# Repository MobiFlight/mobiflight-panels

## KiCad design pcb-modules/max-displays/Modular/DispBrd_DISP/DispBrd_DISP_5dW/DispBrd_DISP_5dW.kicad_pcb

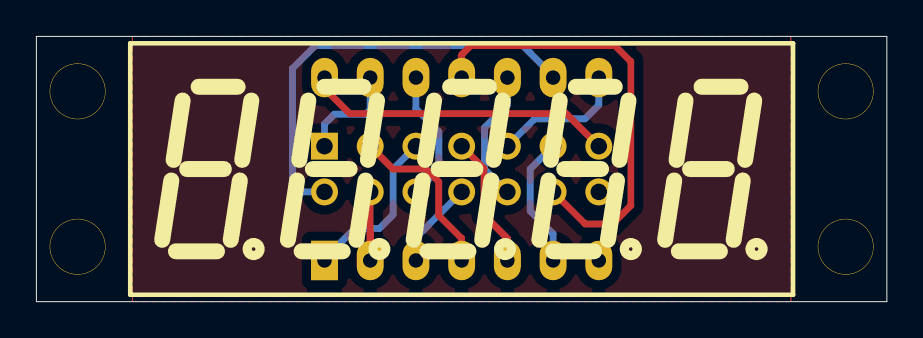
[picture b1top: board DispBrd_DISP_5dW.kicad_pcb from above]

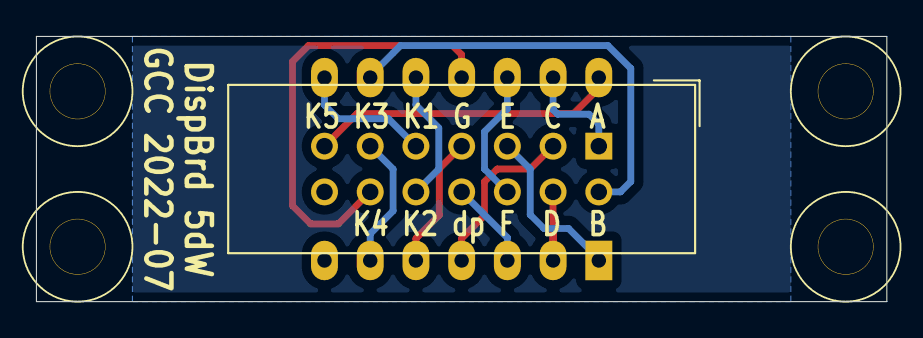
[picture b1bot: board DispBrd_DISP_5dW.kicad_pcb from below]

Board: 2 copper layers, 47.2 x 14.7 mm, 6 parts (5 on the bottom side), 13 nets.

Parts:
H5, H6, H7, H8: MountingHole; Hole3mm
P6: Disp5; IDC-Header_2x07_P2.54mm_Vertical
S4: LEDDSP5_CA; Disp7s5x_036

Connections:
/A0: P6.9, S4.8
/A1: P6.10, S4.10
/A2: P6.11, S4.6
/A3: P6.12, S4.11
/A4: P6.13, S4.14
/K_SegA: P6.1, S4.13
/K_SegB: P6.2, S4.9
/K_SegC: P6.3, S4.4
/K_SegD: P6.4, S4.2
/K_SegDP: P6.8, S4.3
/K_SegE: P6.5, S4.1
/K_SegF: P6.6, S4.12
/K_SegG: P6.7, S4.5

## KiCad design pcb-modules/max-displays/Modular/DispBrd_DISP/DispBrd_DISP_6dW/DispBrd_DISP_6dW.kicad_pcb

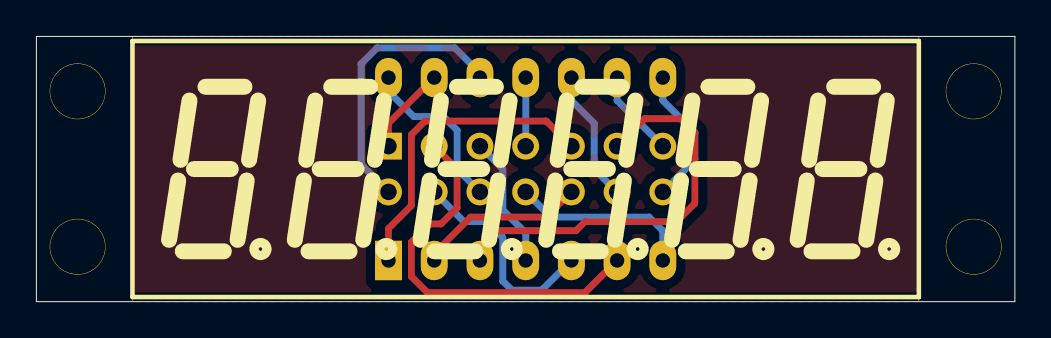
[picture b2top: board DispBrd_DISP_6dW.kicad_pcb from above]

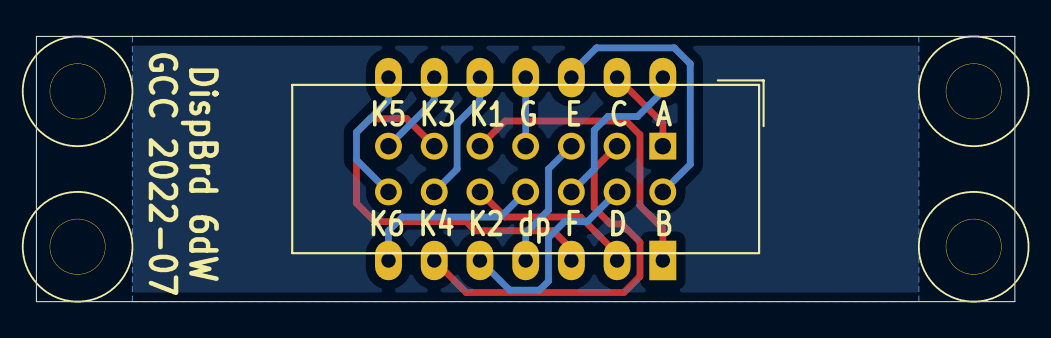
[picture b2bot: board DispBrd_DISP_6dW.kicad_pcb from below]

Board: 2 copper layers, 54.4 x 14.7 mm, 6 parts (5 on the bottom side), 14 nets.

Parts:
H7, H8, H9, H10: MountingHole; Hole3mm
P7: Disp6; IDC-Header_2x07_P2.54mm_Vertical
S5: LEDDSP6_CA; Disp7s6x_036

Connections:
/A0: P7.9, S5.1
/A1: P7.10, S5.2
/A2: P7.11, S5.3
/A3: P7.12, S5.10
/A4: P7.13, S5.9
/A5: P7.14, S5.8
/K_SegA: P7.1, S5.13
/K_SegB: P7.2, S5.12
/K_SegC: P7.3, S5.6
/K_SegD: P7.4, S5.5
/K_SegDP: P7.8, S5.7
/K_SegE: P7.5, S5.4
/K_SegF: P7.6, S5.14
/K_SegG: P7.7, S5.11

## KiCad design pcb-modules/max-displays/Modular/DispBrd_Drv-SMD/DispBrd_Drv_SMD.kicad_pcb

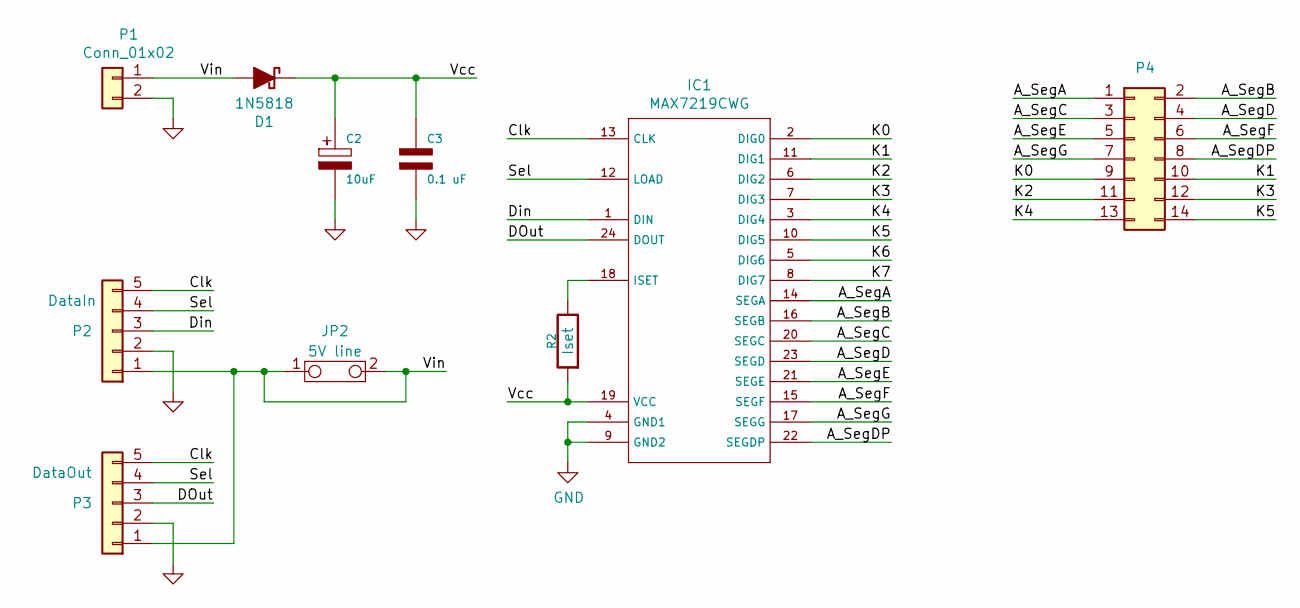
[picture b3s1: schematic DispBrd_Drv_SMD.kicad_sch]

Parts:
C2: 10uF; CP_Radial_D5.0mm_P2.50mm
C3: 0.1 uF; C_1206_3216Metric_Pad1.42x1.75mm_HandSolder
D1: 1N5818; D_SMA_Handsoldering
IC1: MAX7219CWG; SOIC-24W_7.5x15.4mm_P1.27mm
JP2: 5V line; SolderJumper-2_P1.3mm_Bridged_Pad1.0x1.5mm
P1: Conn_01x02; PinHeader_1x02_P2.54mm_Vertical
P2: DataIn; PinHeader_1x05_P2.54mm_Vertical
P3: DataOut; PinHeader_1x05_P2.54mm_Vertical
P4: D0-D5; PinSocket_2x07_P2.54mm_Vertical_SMD
R2: Iset; R_Axial_DIN0207_L6.3mm_D2.5mm_P10.16mm_Horizontal

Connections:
/A_SegA: IC1.14 (SEGA), P4.1
/A_SegB: IC1.16 (SEGB), P4.2
/A_SegC: IC1.20 (SEGC), P4.3
/A_SegD: IC1.23 (SEGD), P4.4
/A_SegDP: IC1.22 (SEGDP), P4.8
/A_SegE: IC1.21 (SEGE), P4.5
/A_SegF: IC1.15 (SEGF), P4.6
/A_SegG: IC1.17 (SEGG), P4.7
/Clk: IC1.13 (CLK), P2.5, P3.5
/DOut: IC1.24 (DOUT), P3.3
/Din: IC1.1 (DIN), P2.3
/K0: IC1.2 (DIG0), P4.9
/K1: IC1.11 (DIG1), P4.10
/K2: IC1.6 (DIG2), P4.11
/K3: IC1.7 (DIG3), P4.12
/K4: IC1.3 (DIG4), P4.13
/K5: IC1.10 (DIG5), P4.14
/K6: IC1.5 (DIG6)
/K7: IC1.8 (DIG7)
/Sel: IC1.12 (LOAD), P2.4, P3.4
/Vcc: C2.1, C3.1, D1.1 (K), IC1.19 (VCC), R2.1
/Vin: D1.2 (A), JP2.1, JP2.2, P1.1, P2.1, P3.1
GND: C2.2, C3.2, IC1.4 (GND1), IC1.9 (GND2), P1.2, P2.2, P3.2
unnamed: IC1.18 (ISET), R2.2

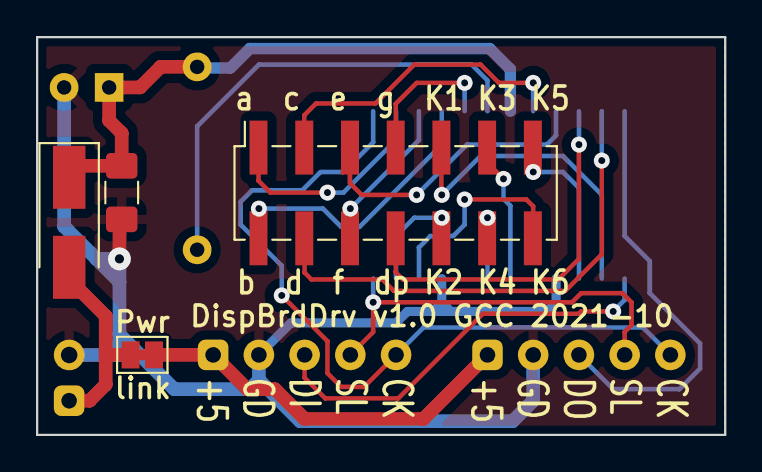
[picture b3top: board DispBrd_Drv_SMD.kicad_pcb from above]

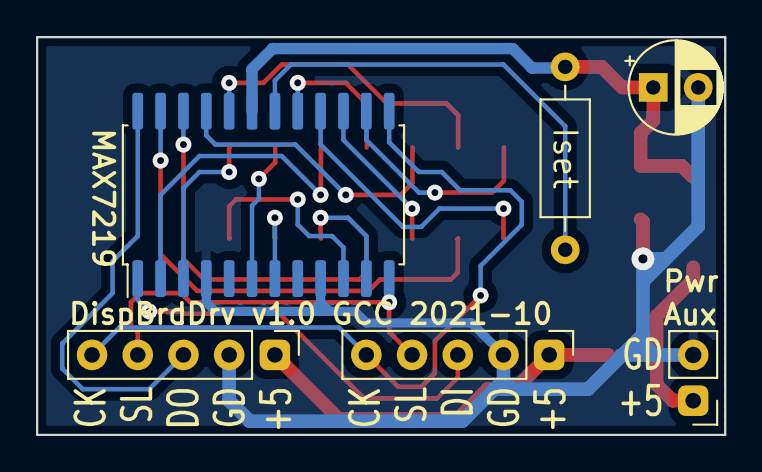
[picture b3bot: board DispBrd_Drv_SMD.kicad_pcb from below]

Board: 2 copper layers, 38.2 x 22.1 mm, 10 parts (6 on the bottom side), 22 nets.

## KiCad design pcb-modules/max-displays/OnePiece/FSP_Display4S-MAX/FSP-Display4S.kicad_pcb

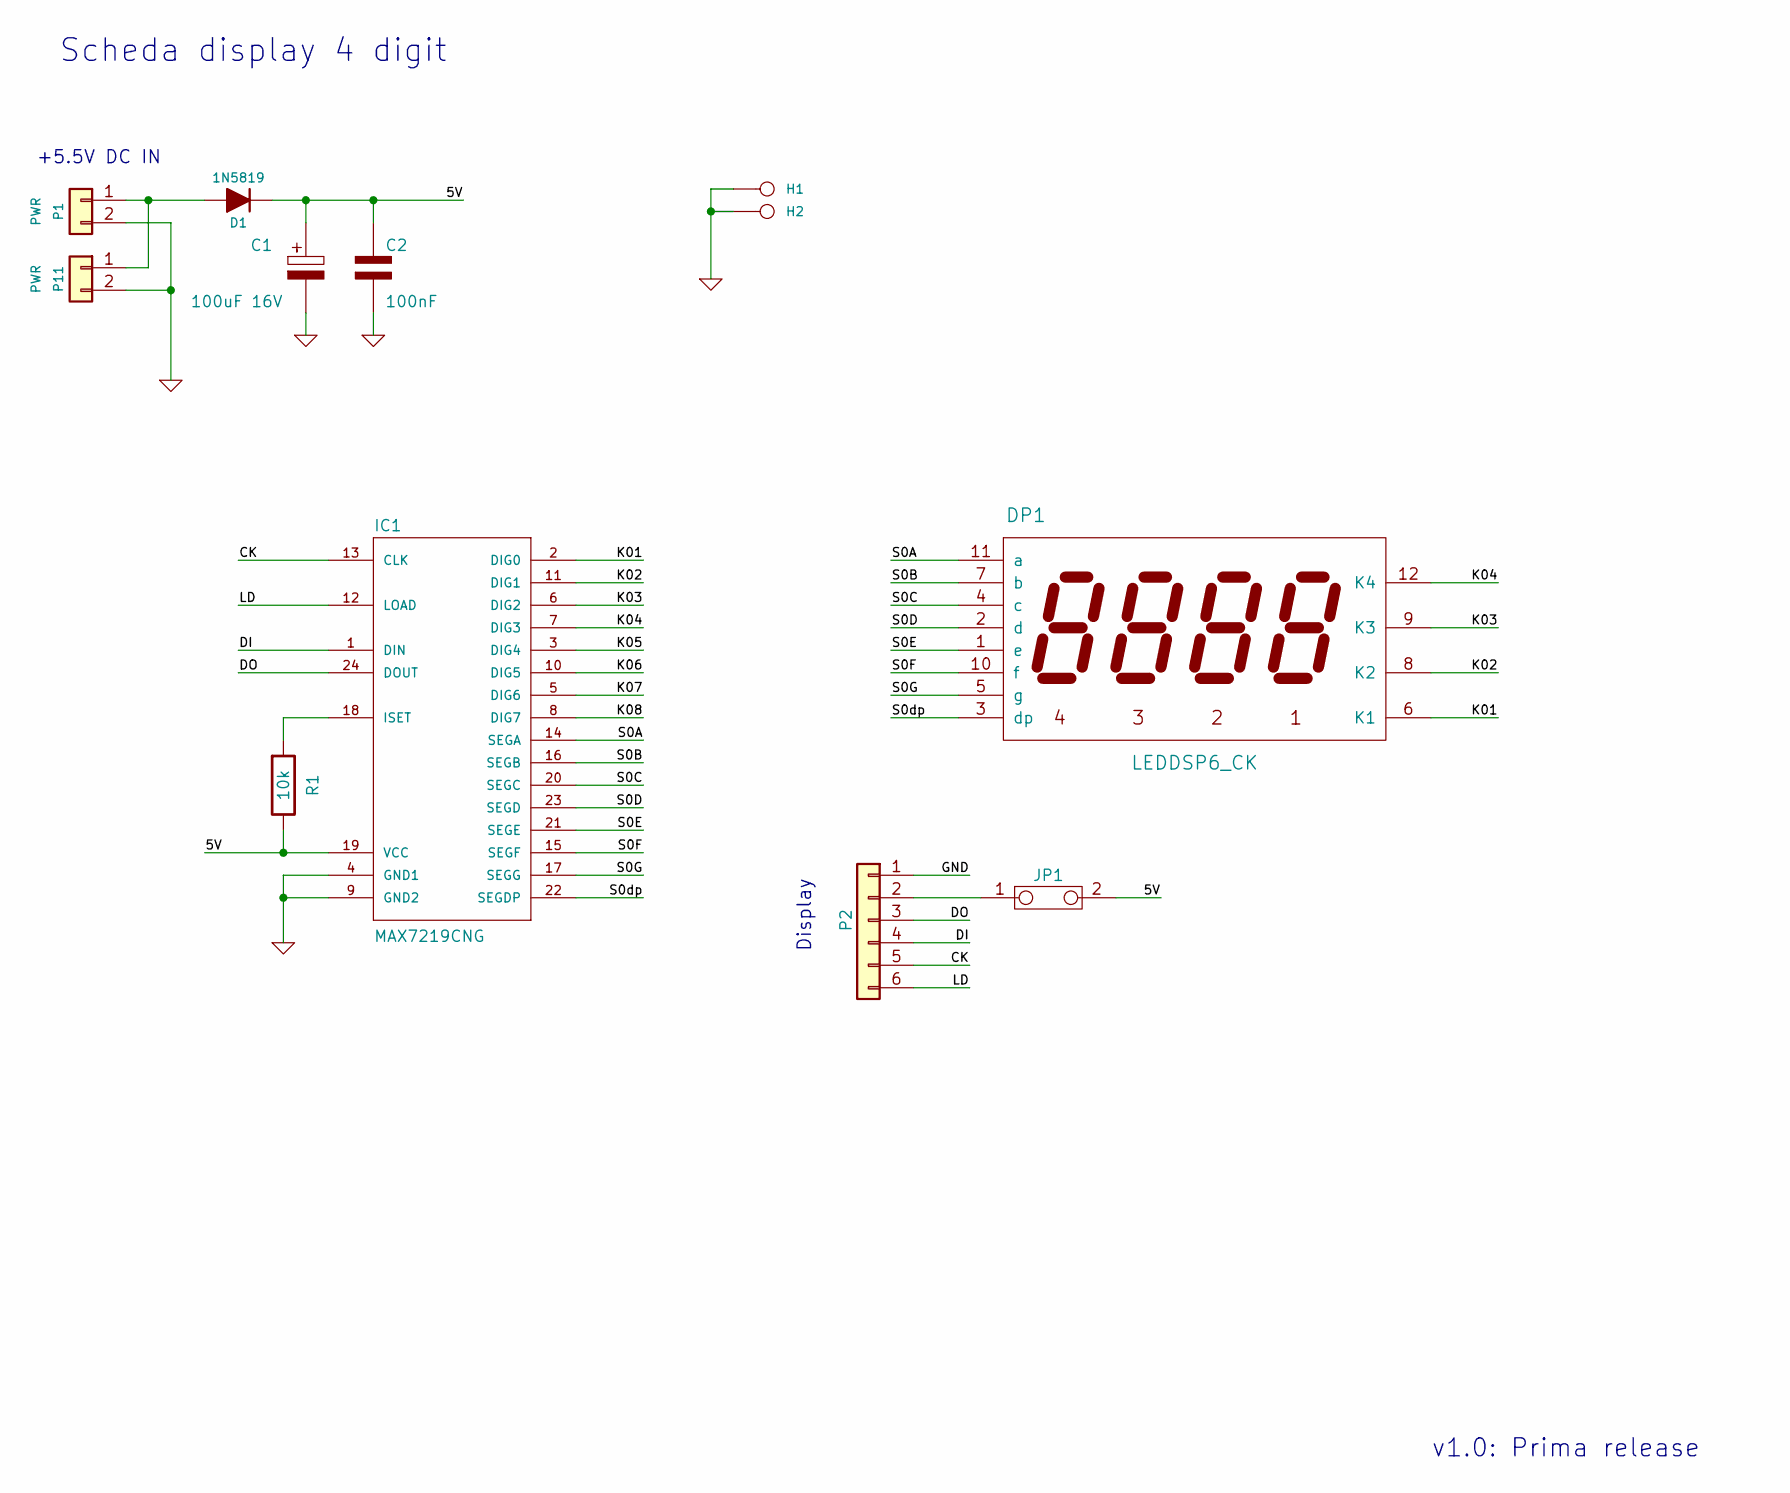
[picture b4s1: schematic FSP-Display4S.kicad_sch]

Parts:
C1: 100uF 16V; CP_Radial_D4.0mm_P2.00mm
C2: 100nF; C_1206_3216Metric_Pad1.33x1.80mm_HandSolder
D1: 1N5819; D_SMA_Handsoldering
DP1: LEDDSP6_CK; Disp7s4x_036
H1, H2: CONN_1; MountingHole_3.2mm_M3
IC1: MAX7219CNG; DIP-24_W7.62mm
JP1: JUMPER2; SolderJumper-2_P1.3mm_Bridged_RoundedPad1.0x1.5mm
P1: PWR; PinHeader_1x02_P2.54mm_Vertical
P2: CONN-6; PinHeader_1x06_P2.54mm_Vertical
P11: PWR; HDR2-3.50+3.81mm
R1: 10k; R_Axial_DIN0207_L6.3mm_D2.5mm_P10.16mm_Horizontal

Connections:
/5V: C1.1, C2.1, D1.1 (K), IC1.19 (VCC), JP1.2, R1.2
/CK: IC1.13 (CLK), P2.5
/DI: IC1.1 (DIN), P2.4
/DO: IC1.24 (DOUT), P2.3
/K01: DP1.6 (K1), IC1.2 (DIG0)
/K02: DP1.8 (K2), IC1.11 (DIG1)
/K03: DP1.9 (K3), IC1.6 (DIG2)
/K04: DP1.12 (K4), IC1.7 (DIG3)
/K05: IC1.3 (DIG4)
/K06: IC1.10 (DIG5)
/K07: IC1.5 (DIG6)
/K08: IC1.8 (DIG7)
/LD: IC1.12 (LOAD), P2.6
/S0A: DP1.11 (a), IC1.14 (SEGA)
/S0B: DP1.7 (b), IC1.16 (SEGB)
/S0C: DP1.4 (c), IC1.20 (SEGC)
/S0D: DP1.2 (d), IC1.23 (SEGD)
/S0E: DP1.1 (e), IC1.21 (SEGE)
/S0F: DP1.10 (f), IC1.15 (SEGF)
/S0G: DP1.5 (g), IC1.17 (SEGG)
/S0dp: DP1.3 (dp), IC1.22 (SEGDP)
GND: C1.2, C2.2, H1.1, H2.1, IC1.4 (GND1), IC1.9 (GND2), P1.2, P2.1, P11.2
unnamed: IC1.18 (ISET), R1.1
unnamed: JP1.1, P2.2
unnamed: D1.2 (A), P1.1, P11.1

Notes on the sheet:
+5.5V DC IN
Scheda display 4 digit
Display
v1.0: Prima release

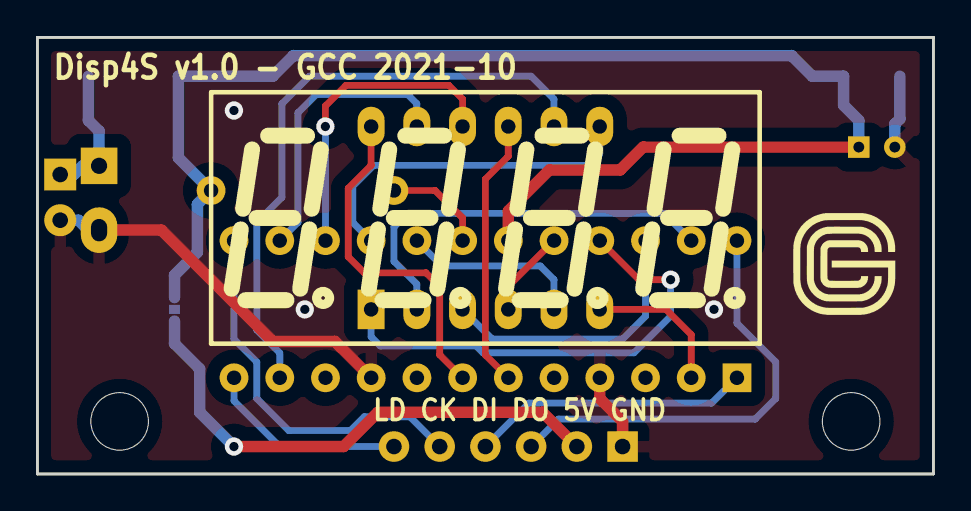
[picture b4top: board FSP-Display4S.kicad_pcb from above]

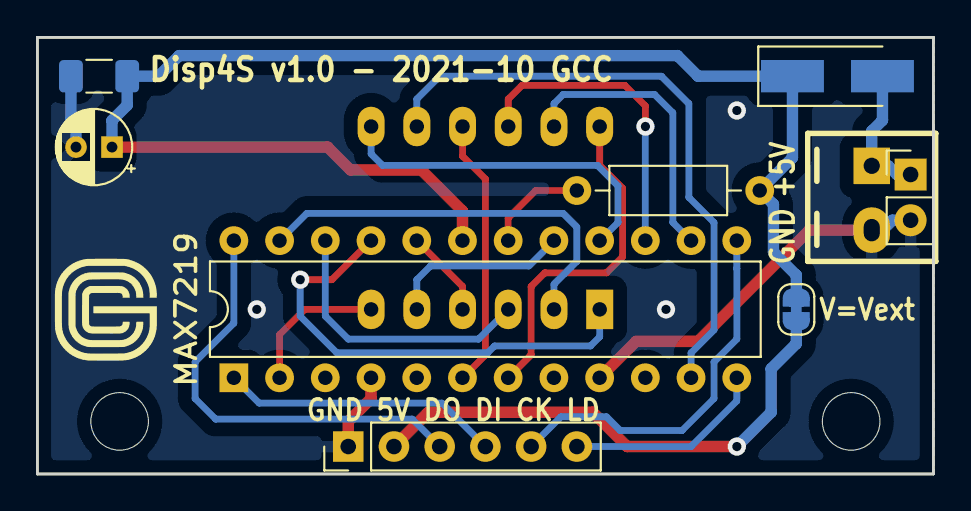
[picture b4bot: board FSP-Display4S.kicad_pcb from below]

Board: 2 copper layers, 49.8 x 24.3 mm, 12 parts (9 on the bottom side), 21 nets.
